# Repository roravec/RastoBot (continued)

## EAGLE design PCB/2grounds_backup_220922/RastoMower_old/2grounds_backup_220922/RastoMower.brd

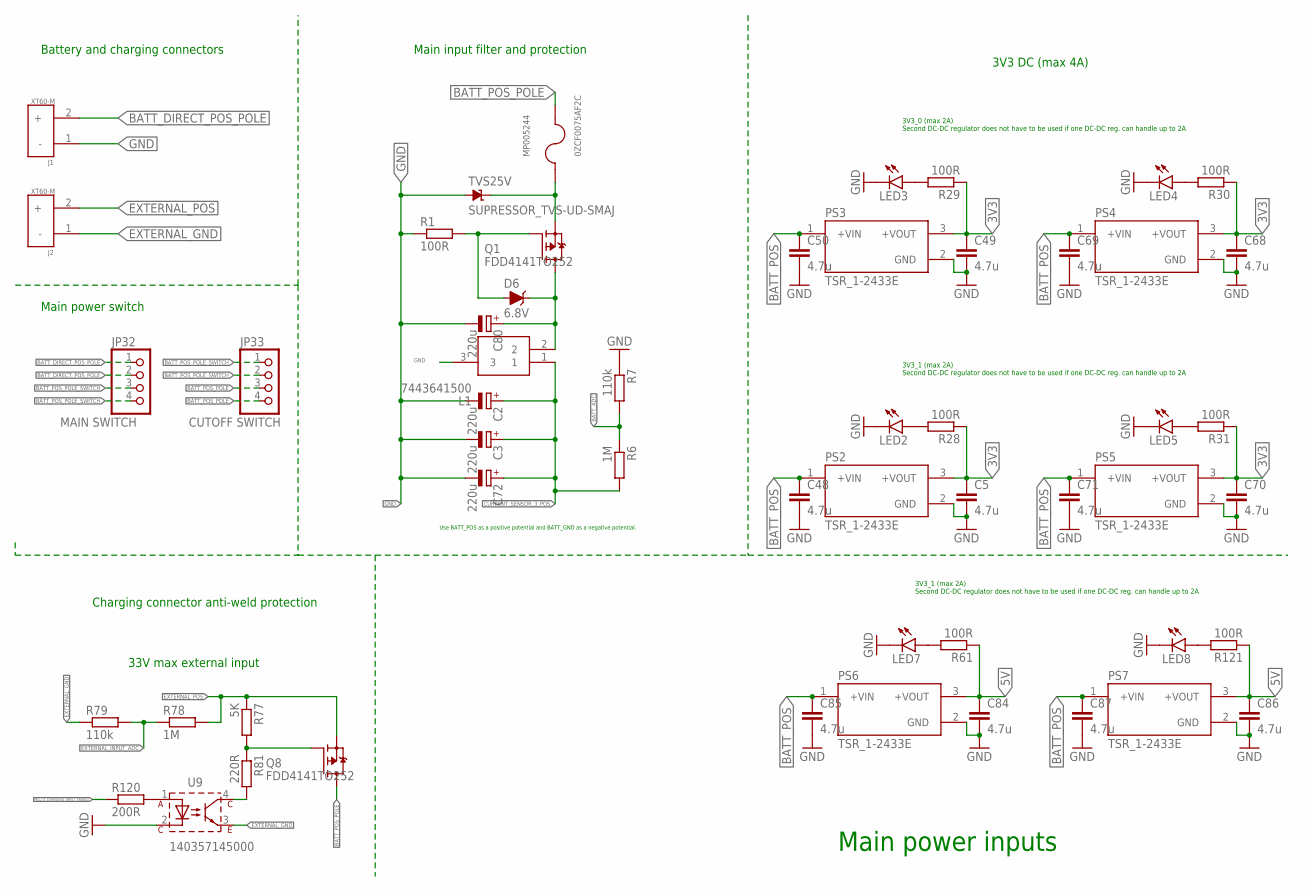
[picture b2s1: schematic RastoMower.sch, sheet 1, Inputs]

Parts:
C2, C3, C72, C80: 220u; E2,5-5
C5, C48, C49, C50, C68, C69, C70, C71, C84, C85, C86, C87: 4.7u; C1206
D6: 6.8V; SOD-323
J1, J2: XT60-M; AMASS_XT60-M
JP32: MAIN SWITCH; 1X04
JP33: CUTOFF SWITCH; 1X04
L1: 7443641500; 74436413300
LED2, LED3, LED4, LED5, LED7, LED8: LEDSML0805; SML0805
MP005244: 0ZCF0075AF2C; FUSE_0ZCF0075AF2C
PS2, PS3, PS4, PS5, PS6, PS7: TSR_1-2433E; CONV_TSR_1-2433E
Q1, Q8: FDD4141TO252; TO252
R1: 100R; R0805
R6, R78: 1M; R0805
R7, R79: 110k; R0805
R28, R29, R30, R31, R61, R121: 100R; R0603
R77: 5K; R0805
R81: 220R; R0805
R120: 200R; R0805
TVS25V: SUPRESSOR_TVS-UD-SMAJ; SUPRESSOR_SMAJ
U9: 140357145000; WL-OCPT_SOP4

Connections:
BATT_ADC: R6.1, R7.2; also elsewhere on the board
BATT_DIRECT_POS_POLE: J1.2 (+), JP32.1, JP32.2
BATT_POS_POLE: JP33.3, JP33.4, MP005244.2, Q8.3 (D)
BATT_POS_POLE_SWITCH: JP32.3, JP32.4, JP33.1, JP33.2
CURRENT_SENSOR_3_POS: C2.+, C3.+, C72.+, L1.1, R6.2; also elsewhere on the board
EXTERNAL_GND: J2.1 (-), R79.1, U9.3
EXTERNAL_INPUT_ADC: R78.1, R79.2; also elsewhere on the board
EXTERNAL_POS: J2.2 (+), Q8.2 (S), R77.1, R78.2
MCU_0_CHARGING_INPUT_ENABLE: R120.1; also elsewhere on the board
unnamed: D6.A, Q1.1 (G), R1.2
unnamed: C80.+, D6.C, L1.2, Q1.3 (D)
unnamed: MP005244.1, Q1.2 (S), TVS25V.C
unnamed: LED2.A, R28.2
unnamed: LED3.A, R29.2
unnamed: LED4.A, R30.2
unnamed: LED5.A, R31.2
unnamed: R120.2, U9.1
unnamed: Q8.1 (G), R77.2, R81.1
unnamed: R81.2, U9.4
unnamed: C84.1, C86.1, PS6.3 (+VOUT), PS7.3 (+VOUT), R61.1, R121.1
unnamed: LED7.A, R61.2
unnamed: LED8.A, R121.2

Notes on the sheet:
33V max external input
Charging connector anti-weld protection
Use BATT_POS as a positive potential and BATT_GND as a negative potential.
Main power inputs
3V3 DC (max 4A)
3V3_0 (max 2A) Second DC-DC regulator does not have to be used if one DC-DC reg. can handle up to 2A
3V3_1 (max 2A) Second DC-DC regulator does not have to be used if one DC-DC reg. can handle up to 2A
Main input filter and protection
Battery and charging connectors
Main power switch

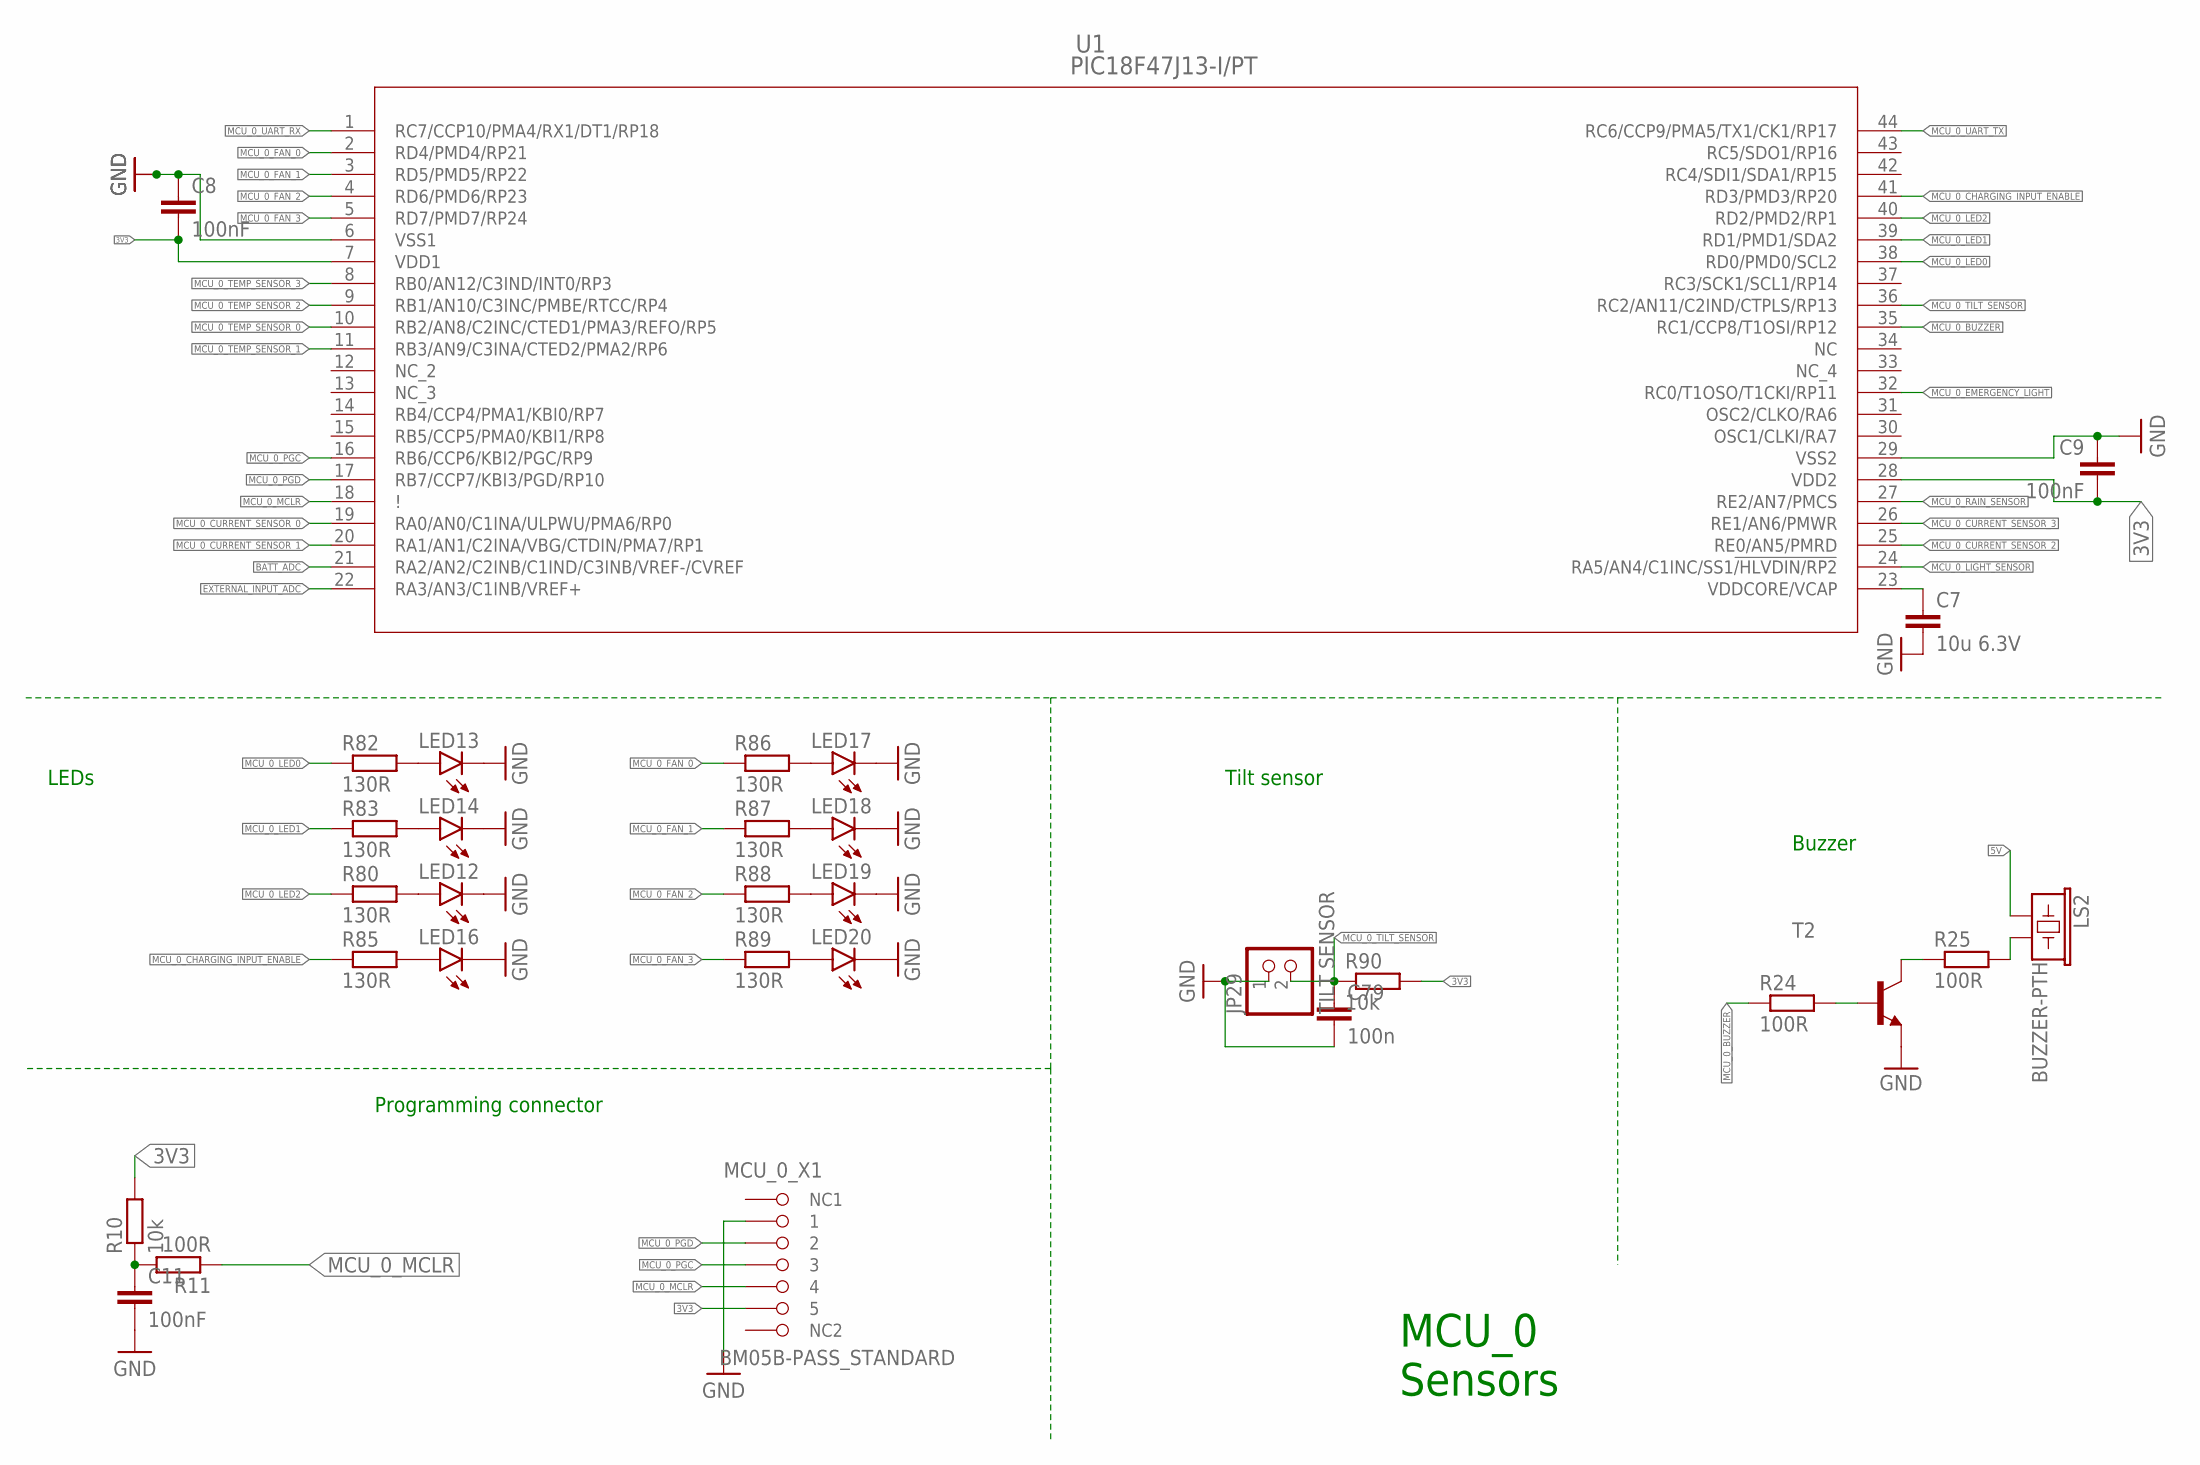
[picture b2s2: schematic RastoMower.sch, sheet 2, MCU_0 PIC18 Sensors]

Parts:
C7: 10u 6.3V; C1206
C8, C9, C11: 100nF; C0603
C79: 100n; C1206
JP29: TILT SENSOR; 1X02
LED12, LED13, LED14, LED16, LED17, LED18, LED19, LED20: LEDSML0805; SML0805
LS2: BUZZER-PTH; BUZZER-12MM
MCU_0_X1: BM05B-PASS_STANDARD; BM05B-PASS
R10: 10k; R0805
R11, R24, R25: 100R; R0805
R80, R82, R83, R85, R86, R87, R88, R89: 130R; R0603
R90: 10k; R0603
T2: BC547-NPN-TO92-CBE; TO92-CBE
U1: PIC18F47J13-I/PT; TQFP44_10X10MC_MCH

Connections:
BATT_ADC: U1.21 (RA2/AN2/C2INB/C1IND/C3INB/VREF-/CVREF); also elsewhere on the board
EXTERNAL_INPUT_ADC: U1.22 (RA3/AN3/C1INB/VREF+); also elsewhere on the board
MCU_0_BUZZER: R24.1, U1.35 (RC1/CCP8/T1OSI/RP12)
MCU_0_CHARGING_INPUT_ENABLE: R85.1, U1.41 (RD3/PMD3/RP20); also elsewhere on the board
MCU_0_CURRENT_SENSOR_0: U1.19 (RA0/AN0/C1INA/ULPWU/PMA6/RP0); also elsewhere on the board
MCU_0_CURRENT_SENSOR_1: U1.20 (RA1/AN1/C2INA/VBG/CTDIN/PMA7/RP1); also elsewhere on the board
MCU_0_CURRENT_SENSOR_2: U1.25 (RE0/AN5/PMRD); also elsewhere on the board
MCU_0_CURRENT_SENSOR_3: U1.26 (RE1/AN6/PMWR); also elsewhere on the board
MCU_0_EMERGENCY_LIGHT: U1.32 (RC0/T1OSO/T1CKI/RP11); also elsewhere on the board
MCU_0_FAN_0: R86.1, U1.2 (RD4/PMD4/RP21); also elsewhere on the board
MCU_0_FAN_1: R87.1, U1.3 (RD5/PMD5/RP22); also elsewhere on the board
MCU_0_FAN_2: R88.1, U1.4 (RD6/PMD6/RP23); also elsewhere on the board
MCU_0_FAN_3: R89.1, U1.5 (RD7/PMD7/RP24); also elsewhere on the board
MCU_0_LED0: R82.1, U1.38 (RD0/PMD0/SCL2)
MCU_0_LED1: R83.1, U1.39 (RD1/PMD1/SDA2)
MCU_0_LED2: R80.1, U1.40 (RD2/PMD2/RP1)
MCU_0_LIGHT_SENSOR: U1.24 (RA5/AN4/C1INC/SS1!/HLVDIN/RP2); also elsewhere on the board
MCU_0_MCLR: MCU_0_X1.P$4 (4), R11.1, U1.18 (!)
MCU_0_PGC: MCU_0_X1.P$3 (3), U1.16 (RB6/CCP6/KBI2/PGC/RP9)
MCU_0_PGD: MCU_0_X1.P$2 (2), U1.17 (RB7/CCP7/KBI3/PGD/RP10)
MCU_0_TEMP_SENSOR_0: U1.10 (RB2/AN8/C2INC/CTED1/PMA3/REFO/RP5); also elsewhere on the board
MCU_0_TEMP_SENSOR_1: U1.11 (RB3/AN9/C3INA/CTED2/PMA2/RP6); also elsewhere on the board
MCU_0_TEMP_SENSOR_2: U1.9 (RB1/AN10/C3INC/PMBE/RTCC/RP4); also elsewhere on the board
MCU_0_TEMP_SENSOR_3: U1.8 (RB0/AN12/C3IND/INT0/RP3); also elsewhere on the board
MCU_0_TILT_SENSOR: C79.1, JP29.2, R90.1, U1.36 (RC2/AN11/C2IND/CTPLS/RP13)
MCU_0_UART_RX: U1.1 (RC7/CCP10/PMA4/RX1/DT1/RP18); also elsewhere on the board
MCU_0_UART_TX: U1.44 (RC6/CCP9/PMA5/TX1/CK1/RP17); also elsewhere on the board
unnamed 121: MCU_0_X1.P$1 (1); also elsewhere on the board
unnamed: C7.1, U1.23 (VDDCORE/VCAP)
unnamed: C11.1, R10.1, R11.2
unnamed: R24.2, T2.B
unnamed: LS2.- (2), R25.2
unnamed: R25.1, T2.C
unnamed: LED12.A, R80.2
unnamed: LED13.A, R82.2
unnamed: LED14.A, R83.2
unnamed: LED16.A, R85.2
unnamed: LED17.A, R86.2
unnamed: LED18.A, R87.2
unnamed: LED19.A, R88.2
unnamed: LED20.A, R89.2

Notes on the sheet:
Buzzer
MCU_0 Sensors
Tilt sensor
LEDs
Programming connector

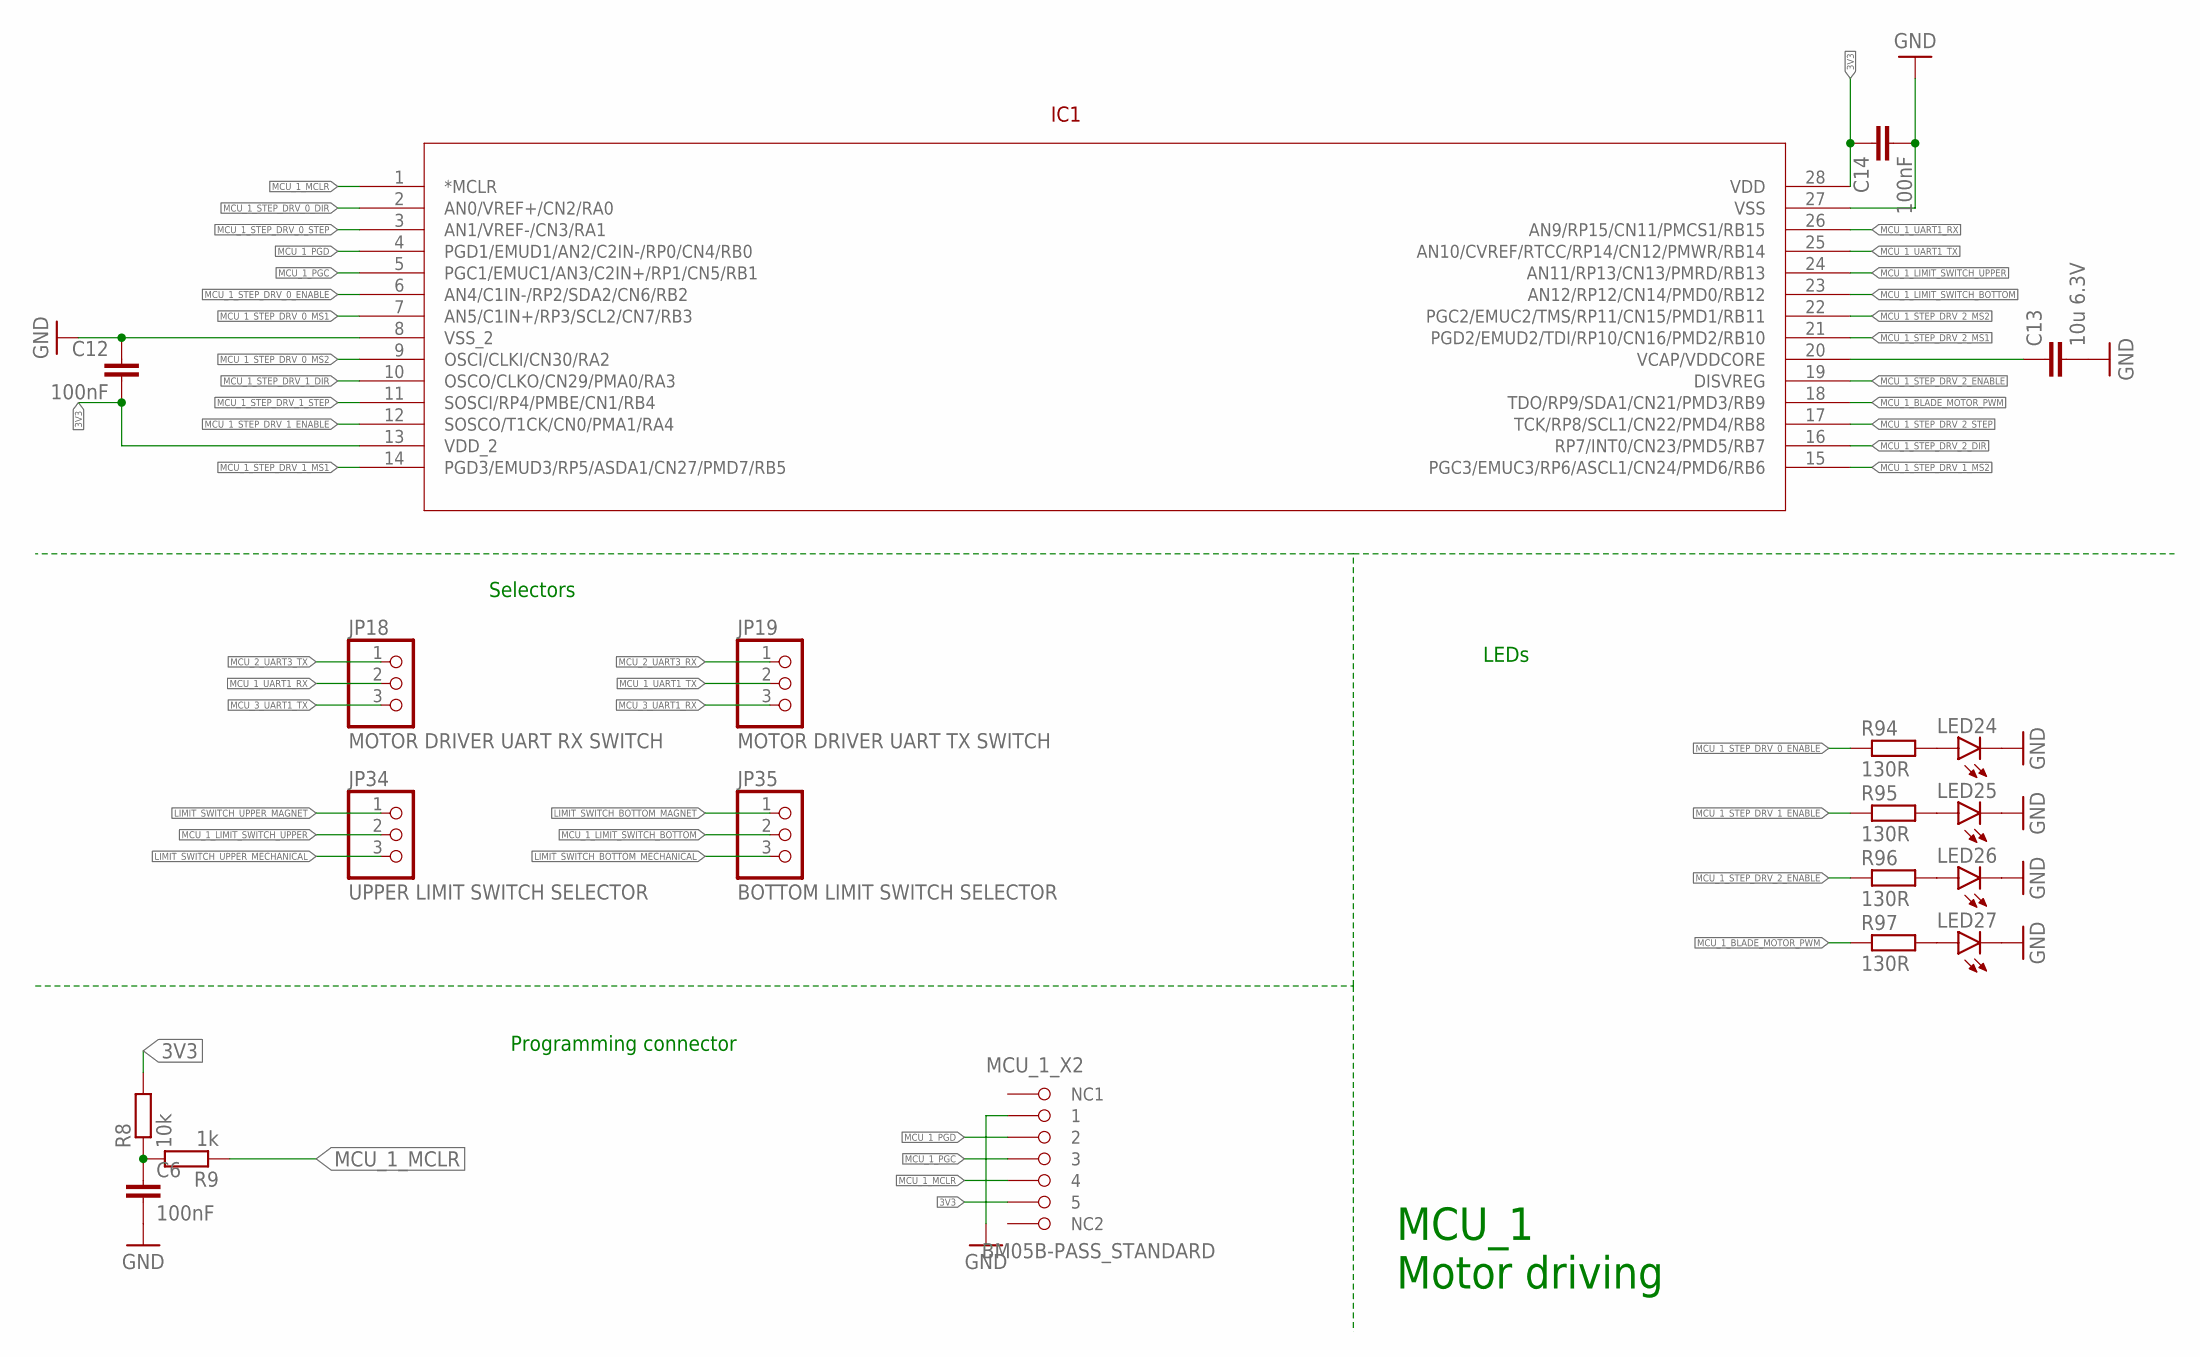
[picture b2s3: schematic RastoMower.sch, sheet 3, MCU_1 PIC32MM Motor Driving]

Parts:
C6, C12, C14: 100nF; C0603
C13: 10u 6.3V; C1206
IC1: PIC24FJ32GA002-X; SPDIP28_300MC
JP18: MOTOR DRIVER UART RX SWITCH; 1X03
JP19: MOTOR DRIVER UART TX SWITCH; 1X03
JP34: UPPER LIMIT SWITCH SELECTOR; 1X03
JP35: BOTTOM LIMIT SWITCH SELECTOR; 1X03
LED24, LED25, LED26, LED27: LEDSML0805; SML0805
MCU_1_X2: BM05B-PASS_STANDARD; BM05B-PASS
R8: 10k; R0805
R9: 1k; R0805
R94, R95, R96, R97: 130R; R0603

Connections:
LIMIT_SWITCH_BOTTOM_MAGNET: JP35.1; also elsewhere on the board
LIMIT_SWITCH_BOTTOM_MECHANICAL: JP35.3; also elsewhere on the board
LIMIT_SWITCH_UPPER_MAGNET: JP34.1; also elsewhere on the board
LIMIT_SWITCH_UPPER_MECHANICAL: JP34.3; also elsewhere on the board
MCU_1_BLADE_MOTOR_PWM: IC1.18 (TDO/RP9/SDA1/CN21/PMD3/RB9), R97.1; also elsewhere on the board
MCU_1_LIMIT_SWITCH_BOTTOM: IC1.23 (AN12/RP12/CN14/PMD0/RB12), JP35.2
MCU_1_LIMIT_SWITCH_UPPER: IC1.24 (AN11/RP13/CN13/PMRD/RB13), JP34.2
MCU_1_MCLR: IC1.1 (*MCLR), MCU_1_X2.P$4 (4), R9.1
MCU_1_PGC: IC1.5 (PGC1/EMUC1/AN3/C2IN+/RP1/CN5/RB1), MCU_1_X2.P$3 (3)
MCU_1_PGD: IC1.4 (PGD1/EMUD1/AN2/C2IN-/RP0/CN4/RB0), MCU_1_X2.P$2 (2)
MCU_1_STEP_DRV_0_DIR: IC1.2 (AN0/VREF+/CN2/RA0); also elsewhere on the board
MCU_1_STEP_DRV_0_ENABLE: IC1.6 (AN4/C1IN-/RP2/SDA2/CN6/RB2), R94.1; also elsewhere on the board
MCU_1_STEP_DRV_0_MS1: IC1.7 (AN5/C1IN+/RP3/SCL2/CN7/RB3); also elsewhere on the board
MCU_1_STEP_DRV_0_MS2: IC1.9 (OSCI/CLKI/CN30/RA2); also elsewhere on the board
MCU_1_STEP_DRV_0_STEP: IC1.3 (AN1/VREF-/CN3/RA1); also elsewhere on the board
MCU_1_STEP_DRV_1_DIR: IC1.10 (OSCO/CLKO/CN29/PMA0/RA3); also elsewhere on the board
MCU_1_STEP_DRV_1_ENABLE: IC1.12 (SOSCO/T1CK/CN0/PMA1/RA4), R95.1; also elsewhere on the board
MCU_1_STEP_DRV_1_MS1: IC1.14 (PGD3/EMUD3/RP5/ASDA1/CN27/PMD7/RB5); also elsewhere on the board
MCU_1_STEP_DRV_1_MS2: IC1.15 (PGC3/EMUC3/RP6/ASCL1/CN24/PMD6/RB6); also elsewhere on the board
MCU_1_STEP_DRV_1_STEP: IC1.11 (SOSCI/RP4/PMBE/CN1/RB4); also elsewhere on the board
MCU_1_STEP_DRV_2_DIR: IC1.16 (RP7/INT0/CN23/PMD5/RB7); also elsewhere on the board
MCU_1_STEP_DRV_2_ENABLE: IC1.19 (DISVREG), R96.1; also elsewhere on the board
MCU_1_STEP_DRV_2_MS1: IC1.21 (PGD2/EMUD2/TDI/RP10/CN16/PMD2/RB10); also elsewhere on the board
MCU_1_STEP_DRV_2_MS2: IC1.22 (PGC2/EMUC2/TMS/RP11/CN15/PMD1/RB11); also elsewhere on the board
MCU_1_STEP_DRV_2_STEP: IC1.17 (TCK/RP8/SCL1/CN22/PMD4/RB8); also elsewhere on the board
MCU_1_UART1_RX: IC1.26 (AN9/RP15/CN11/PMCS1/RB15), JP18.2
MCU_1_UART1_TX: IC1.25 (AN10/CVREF/RTCC/RP14/CN12/PMWR/RB14), JP19.2
MCU_2_UART3_RX: JP19.1; also elsewhere on the board
MCU_2_UART3_TX: JP18.1; also elsewhere on the board
MCU_3_UART1_RX: JP19.3; also elsewhere on the board
MCU_3_UART1_TX: JP18.3; also elsewhere on the board
unnamed 121: MCU_1_X2.P$1 (1); also elsewhere on the board
unnamed: C6.1, R8.1, R9.2
unnamed: C13.1, IC1.20 (VCAP/VDDCORE)
unnamed: LED24.A, R94.2
unnamed: LED25.A, R95.2
unnamed: LED26.A, R96.2
unnamed: LED27.A, R97.2

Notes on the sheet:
MCU_1 Motor driving
LEDs
Programming connector
Selectors

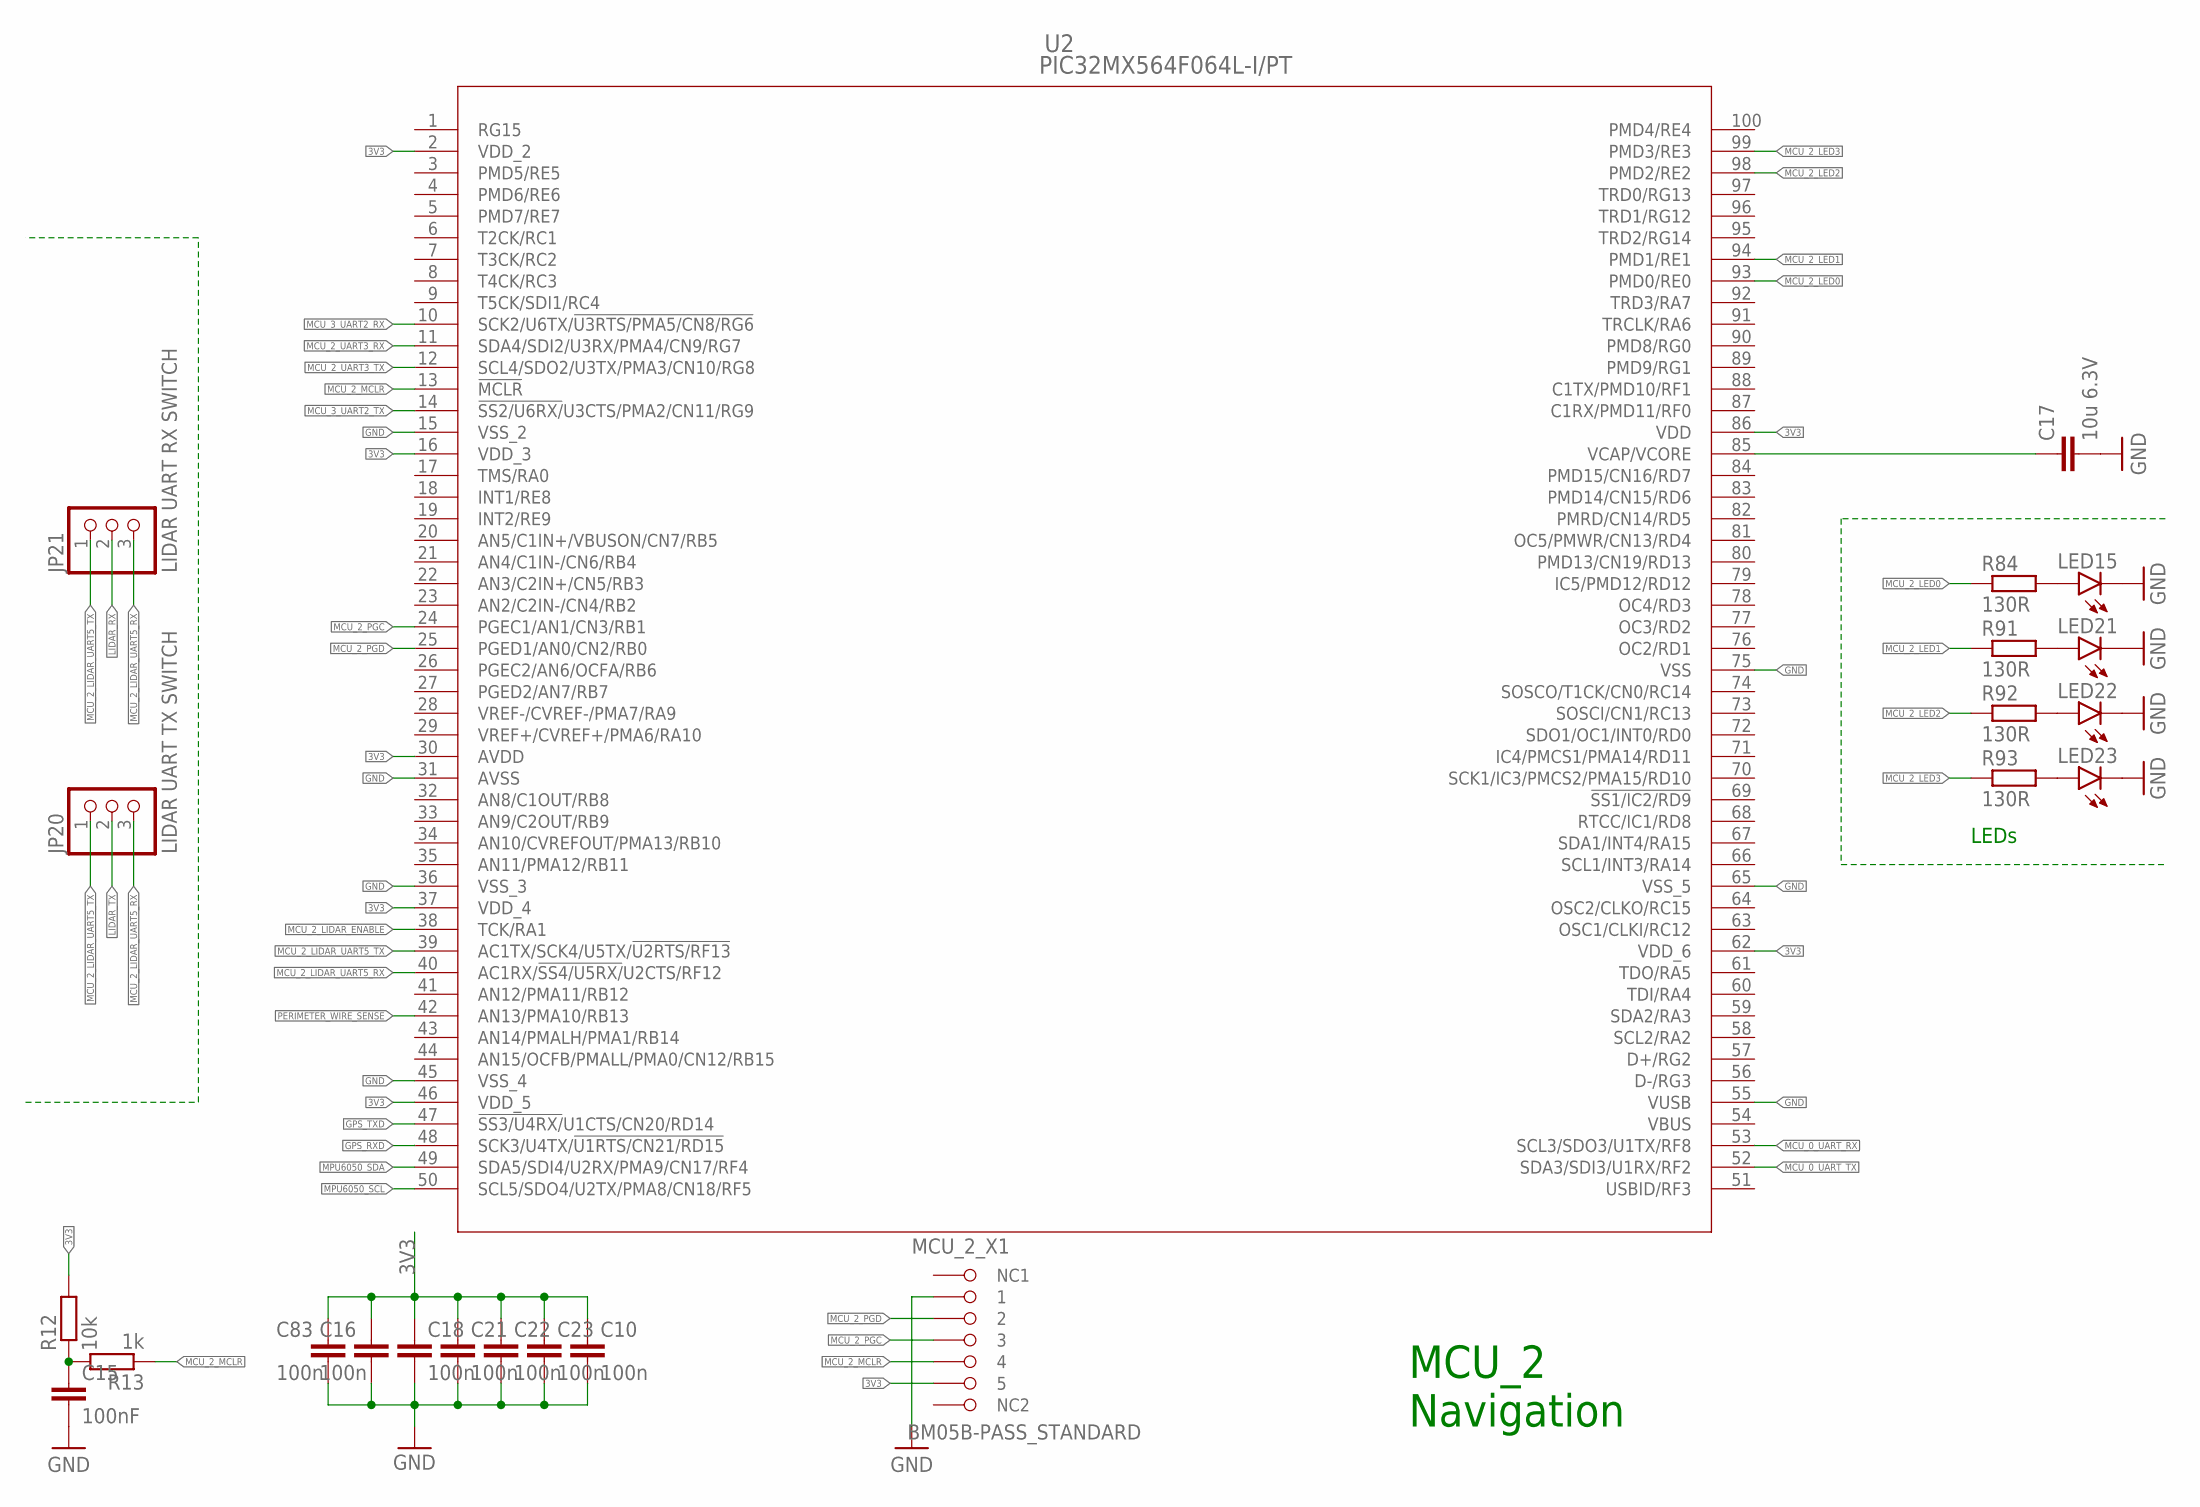
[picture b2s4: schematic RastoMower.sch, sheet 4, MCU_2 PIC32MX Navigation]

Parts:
C10, C16, C18, C21, C22, C23, C83: 100n; C0603
C15: 100nF; C0603
C17: 10u 6.3V; C1206
JP20: LIDAR UART TX SWITCH; 1X03
JP21: LIDAR UART RX SWITCH; 1X03
LED15, LED21, LED22, LED23: LEDSML0805; SML0805
MCU_2_X1: BM05B-PASS_STANDARD; BM05B-PASS
R12: 10k; R0805
R13: 1k; R0805
R84, R91, R92, R93: 130R; R0603
U2: PIC32MX564F064L-I/PT; TQFP100_12X12MC_MCH

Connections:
GPS_RXD: U2.48 (SCK3/U4TX/!U1RTS/CN21/RD15); also elsewhere on the board
GPS_TXD: U2.47 (!SS3/U4RX/!U1CTS/CN20/RD14); also elsewhere on the board
LIDAR_RX: JP21.2; also elsewhere on the board
LIDAR_TX: JP20.2; also elsewhere on the board
MCU_0_UART_RX: U2.53 (SCL3/SDO3/U1TX/RF8); also elsewhere on the board
MCU_0_UART_TX: U2.52 (SDA3/SDI3/U1RX/RF2); also elsewhere on the board
MCU_2_LED0: R84.1, U2.93 (PMD0/RE0)
MCU_2_LED1: R91.1, U2.94 (PMD1/RE1)
MCU_2_LED2: R92.1, U2.98 (PMD2/RE2)
MCU_2_LED3: R93.1, U2.99 (PMD3/RE3)
MCU_2_LIDAR_ENABLE: U2.38 (TCK/RA1); also elsewhere on the board
MCU_2_LIDAR_UART5_RX: JP20.3, JP21.3, U2.40 (AC1RX/!SS4/U5RX/!U2CTS/RF12)
MCU_2_LIDAR_UART5_TX: JP20.1, JP21.1, U2.39 (AC1TX/SCK4/U5TX/!U2RTS/RF13)
MCU_2_MCLR: MCU_2_X1.P$4 (4), R13.1, U2.13 (!MCLR)
MCU_2_PGC: MCU_2_X1.P$3 (3), U2.24 (PGEC1/AN1/CN3/RB1)
MCU_2_PGD: MCU_2_X1.P$2 (2), U2.25 (PGED1/AN0/CN2/RB0)
MCU_2_UART3_RX: U2.11 (SDA4/SDI2/U3RX/PMA4/CN9/RG7); also elsewhere on the board
MCU_2_UART3_TX: U2.12 (SCL4/SDO2/U3TX/PMA3/CN10/RG8); also elsewhere on the board
MCU_3_UART2_RX: U2.10 (SCK2/U6TX/!U3RTS/PMA5/CN8/RG6); also elsewhere on the board
MCU_3_UART2_TX: U2.14 (!SS2/U6RX/!U3CTS/PMA2/CN11/RG9); also elsewhere on the board
MPU6050_SCL: U2.50 (SCL5/SDO4/U2TX/PMA8/CN18/RF5); also elsewhere on the board
MPU6050_SDA: U2.49 (SDA5/SDI4/U2RX/PMA9/CN17/RF4); also elsewhere on the board
unnamed 121: MCU_2_X1.P$1 (1); also elsewhere on the board
unnamed: C17.1, U2.85 (VCAP/VCORE)
unnamed: C15.1, R12.1, R13.2
unnamed: LED15.A, R84.2
unnamed: LED21.A, R91.2
unnamed: LED22.A, R92.2
unnamed: LED23.A, R93.2
PERIMETER_WIRE_SENSE: U2.42 (AN13/PMA10/RB13); also elsewhere on the board
VBUS: U2.54 (VBUS)

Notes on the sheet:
MCU_2 Navigation
LEDs

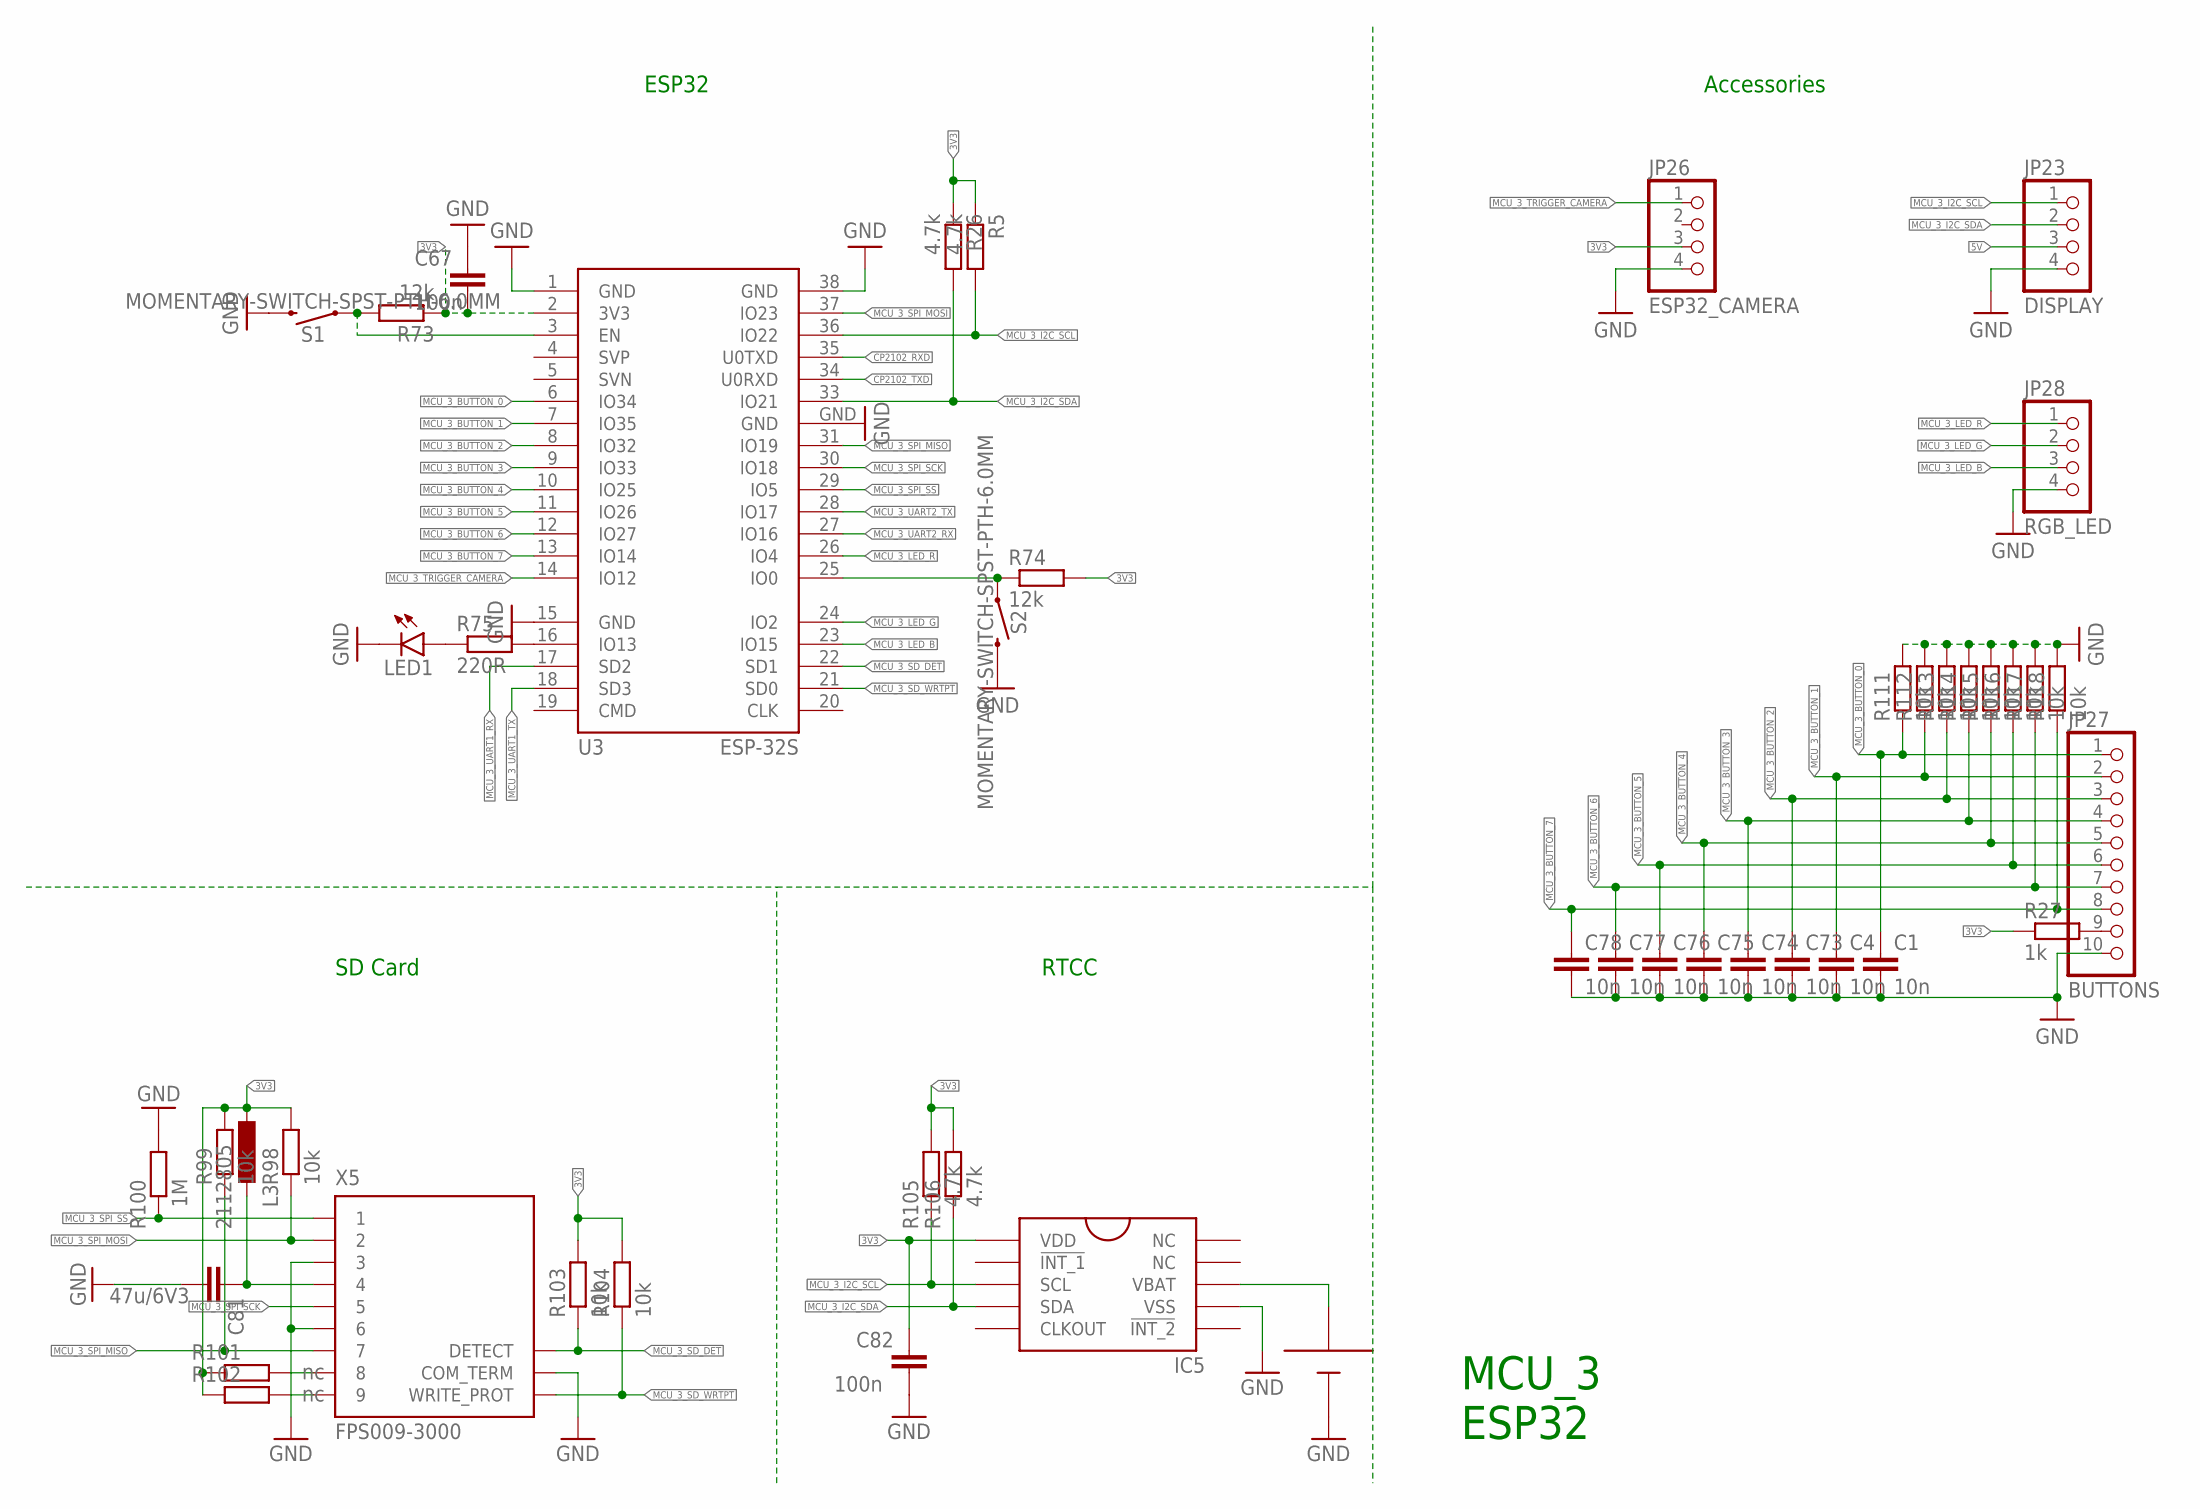
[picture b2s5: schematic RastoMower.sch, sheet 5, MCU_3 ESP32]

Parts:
BATT1: SMTU2032LF
C1, C4, C73, C74, C75, C76, C77, C78: 10n; C0603
C67, C82: 100n; C0603
C81: 47u/6V3; C1206
IC5: AB-RTCMC-32.768KHZ-B5ZE-S3-T
JP23: DISPLAY; 1X04
JP26: ESP32_CAMERA; 1X04
JP27: BUTTONS; 1X10
JP28: RGB_LED; 1X04
L3: 2112805; L2825P
LED1: LEDSML0805; SML0805
R5, R26, R105, R106: 4.7k; R0603
R27: 1k; R0603
R73, R74: 12k; R0805
R75: 220R; R0805
R98, R99, R103, R104, R111, R112, R113, R114, R115, R116, R117, R118: 10k; R0603
R100: 1M; R0603
R101, R102: nc; R0603
S1, S2: MOMENTARY-SWITCH-SPST-PTH-6.0MM; TACTILE_SWITCH_PTH_6.0MM
U3: ESP-32S
X5: FPS009-3000

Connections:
CP2102_RXD: U3.35 (U0TXD); also elsewhere on the board
CP2102_TXD: U3.34 (U0RXD); also elsewhere on the board
MCU_3_BUTTON_0: C1.1, JP27.1, R111.1, U3.6 (IO34)
MCU_3_BUTTON_1: C4.1, JP27.2, R112.1, U3.7 (IO35)
MCU_3_BUTTON_2: C73.1, JP27.3, R113.1, U3.8 (IO32)
MCU_3_BUTTON_3: C74.1, JP27.4, R114.1, U3.9 (IO33)
MCU_3_BUTTON_4: C75.1, JP27.5, R115.1, U3.10 (IO25)
MCU_3_BUTTON_5: C76.1, JP27.6, R116.1, U3.11 (IO26)
MCU_3_BUTTON_6: C77.1, JP27.7, R117.1, U3.12 (IO27)
MCU_3_BUTTON_7: C78.1, JP27.8, R118.1, U3.13 (IO14)
MCU_3_I2C_SCL: IC5.3 (SCL), JP23.1, R5.2, R105.1, U3.36 (IO22)
MCU_3_I2C_SDA: IC5.4 (SDA), JP23.2, R26.2, R106.1, U3.33 (IO21)
MCU_3_LED_B: JP28.3, U3.23 (IO15)
MCU_3_LED_G: JP28.2, U3.24 (IO2)
MCU_3_LED_R: JP28.1, U3.26 (IO4)
MCU_3_SD_DET: R103.1, U3.22 (SD1), X5.DETECT
MCU_3_SD_WRTPT: R104.1, U3.21 (SD0), X5.WRITE_PROT
MCU_3_SPI_MISO: R99.1, U3.31 (IO19), X5.7
MCU_3_SPI_MOSI: R98.1, U3.37 (IO23), X5.2
MCU_3_SPI_SCK: U3.30 (IO18), X5.5
MCU_3_SPI_SS: R100.1, U3.29 (IO5), X5.1
MCU_3_TRIGGER_CAMERA: JP26.1, U3.14 (IO12)
MCU_3_UART1_RX: U3.17 (SD2); also elsewhere on the board
MCU_3_UART1_TX: U3.18 (SD3); also elsewhere on the board
MCU_3_UART2_RX: U3.27 (IO16); also elsewhere on the board
MCU_3_UART2_TX: U3.28 (IO17); also elsewhere on the board
unnamed: JP27.9, R27.2
unnamed: R74.1, S2.1, U3.25 (IO0)
unnamed: R73.2, S1.1, U3.3 (EN)
unnamed: R75.2, U3.16 (IO13)
unnamed: LED1.A, R75.1
unnamed: R102.2, X5.9
unnamed: R101.2, X5.8
unnamed: BATT1.PLUS, IC5.8 (VBAT)
unnamed: C81.1, L3.1, X5.4

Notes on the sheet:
SD Card
RTCC
Accessories
ESP32
MCU_3 ESP32
